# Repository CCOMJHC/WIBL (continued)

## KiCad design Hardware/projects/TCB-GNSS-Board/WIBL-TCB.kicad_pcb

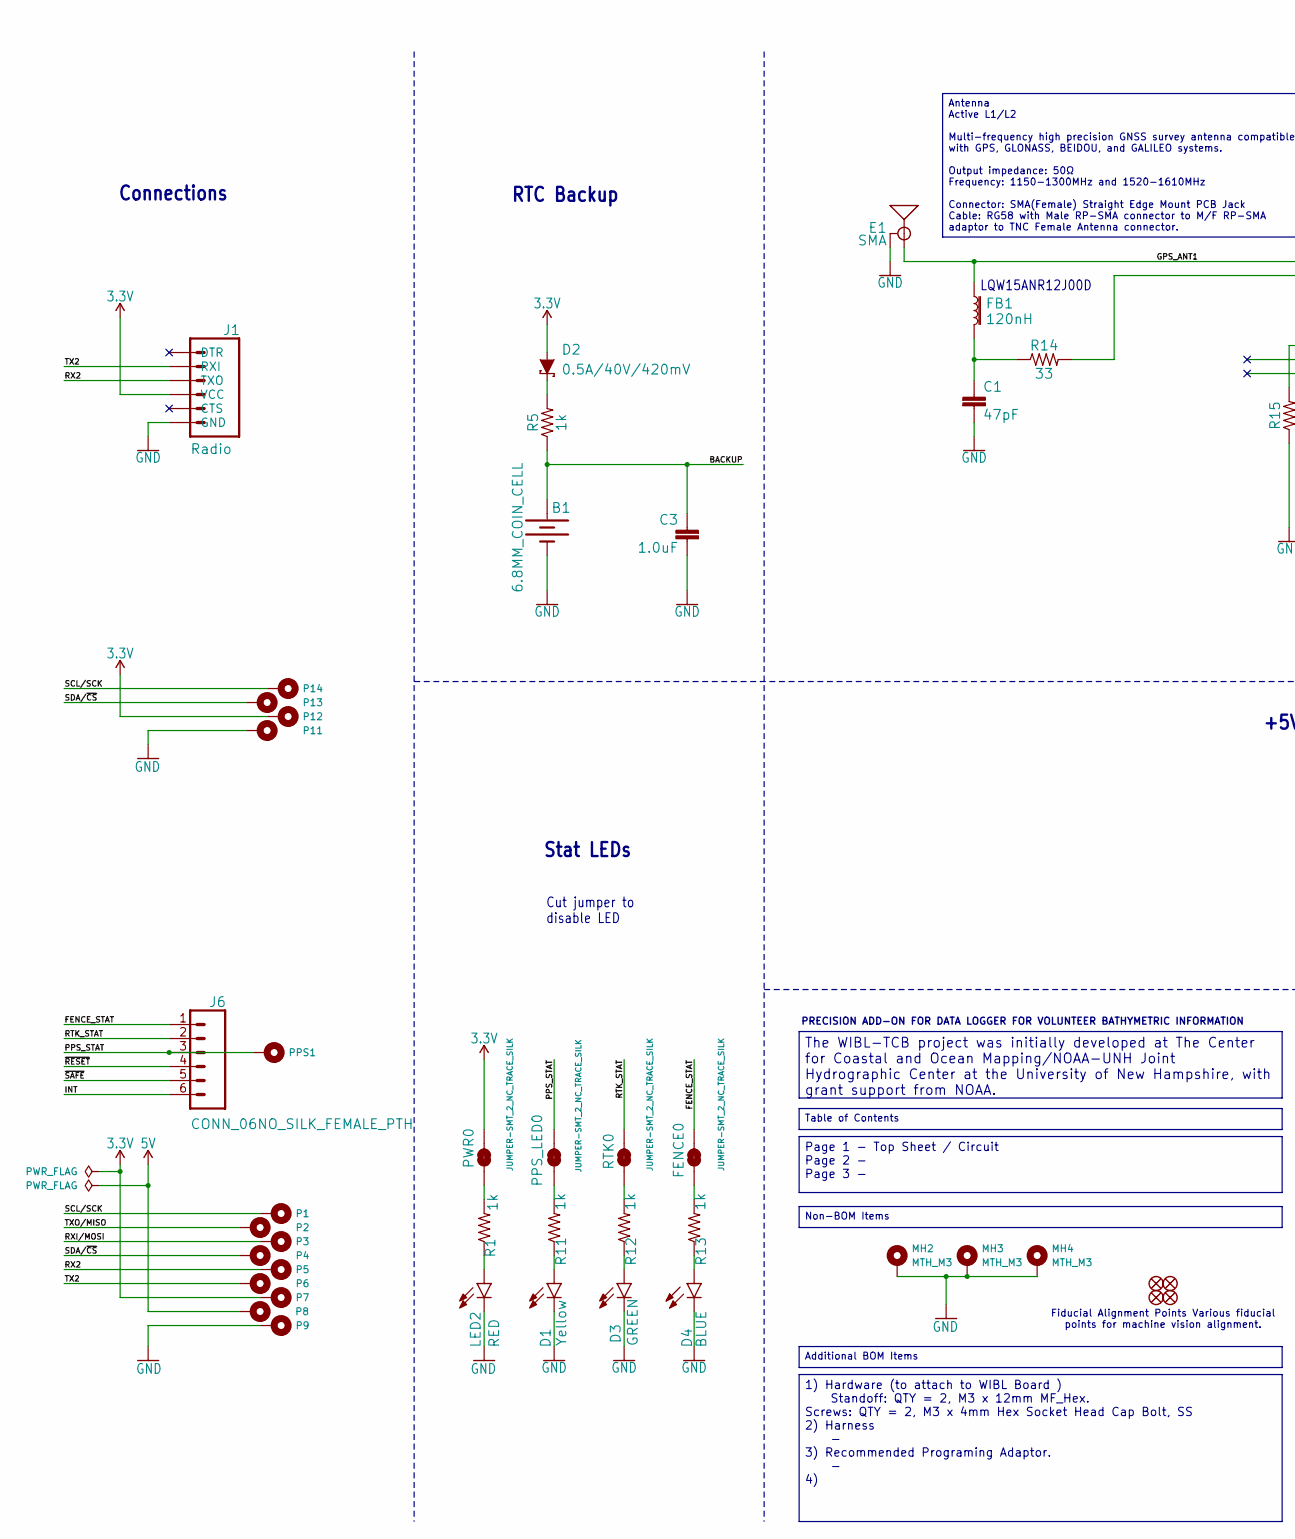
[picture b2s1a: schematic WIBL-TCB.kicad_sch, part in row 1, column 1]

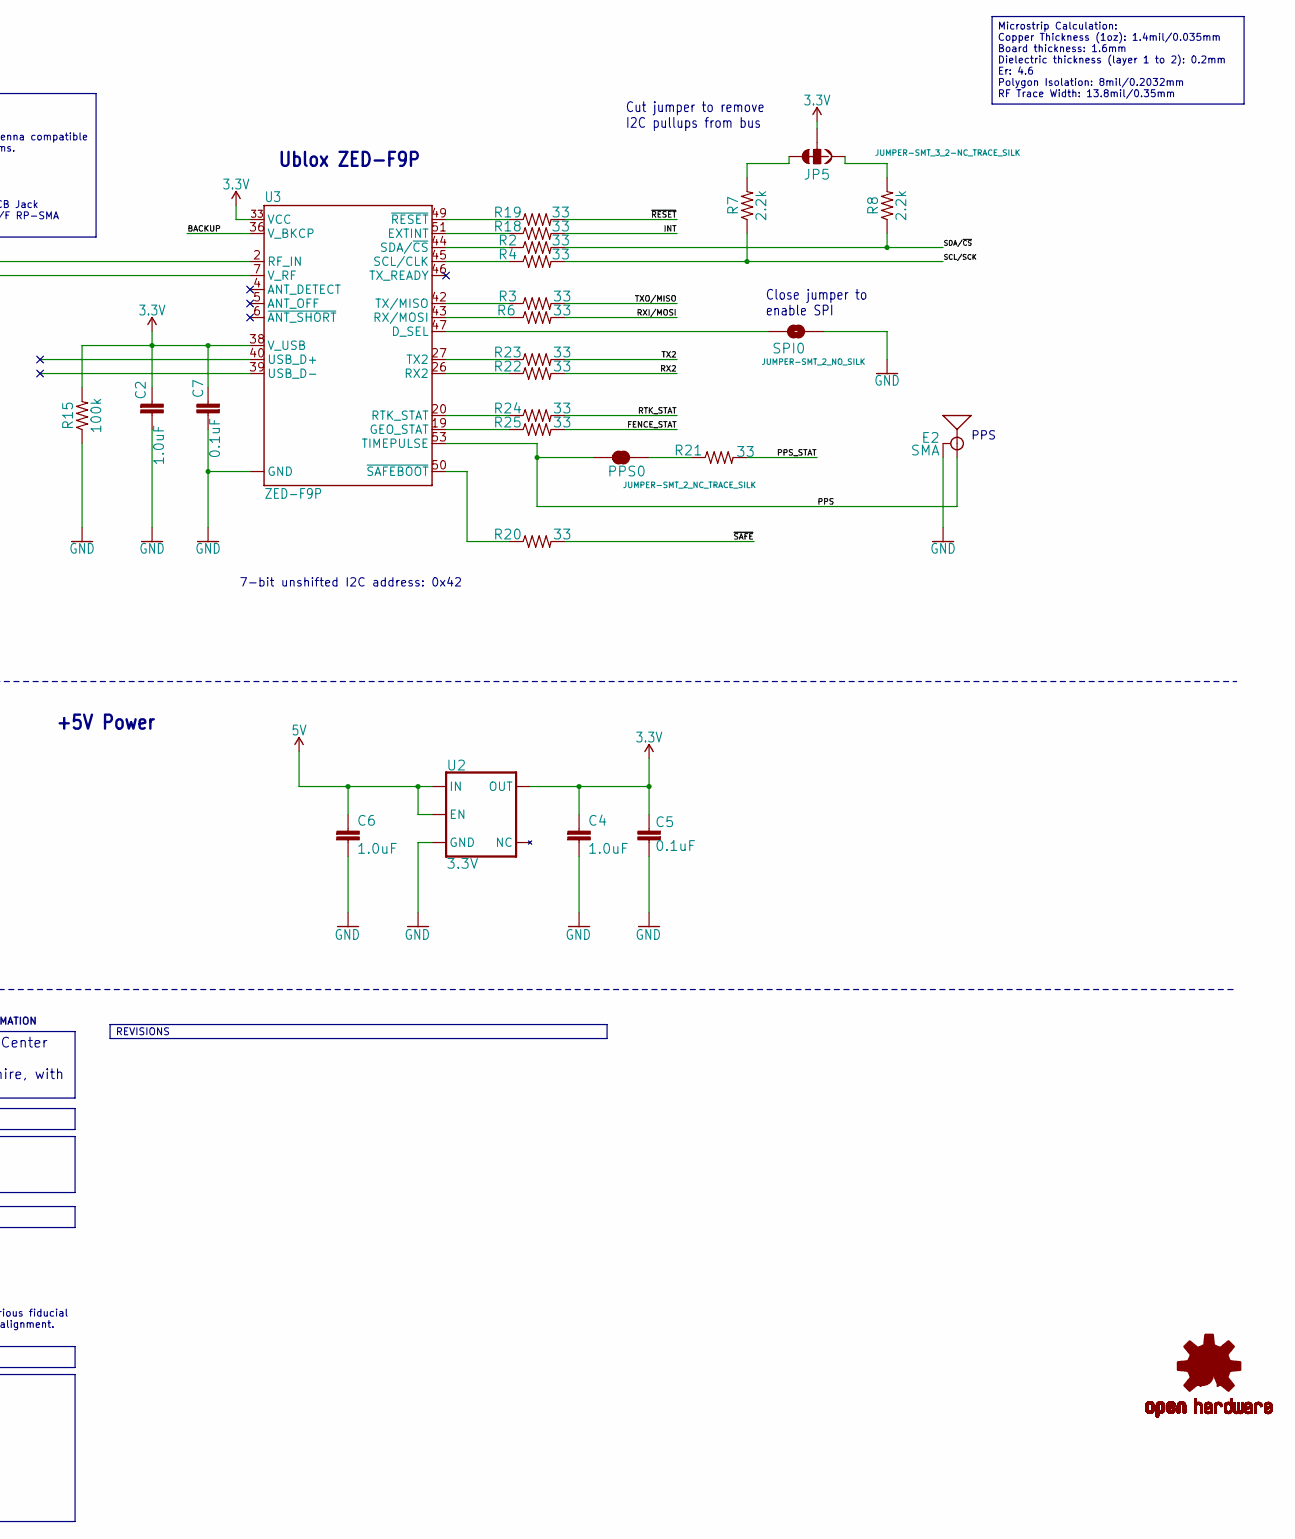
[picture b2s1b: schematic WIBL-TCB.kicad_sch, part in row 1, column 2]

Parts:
B1: 6.8MM_COIN_CELL; ML414H_IV01E_TBC; MPNum ML414H IV01E
C1: 47pF; 0402; MPNum CC0402KRNPO9BN470
C2, C3, C4, C6: 1.0uF; 0603; MPNum CL10B105KP8NNNC
C5, C7: 0.1uF; 0603; MPNum CC0603KRX7R9BB104
D1: Yellow; LED-0603; MPNum XL-1608UYC-06
D2: 0.5A/40V/420mV; SOD-323; MPNum 1N5819WS
D3: GREEN; LED-0603; MPNum LTST-C190GKT
D4: BLUE; LED-0603; MPNum LTST-C193TBKT-5A
E1, E2: SMA; SMA-EDGE; MPNum CON-SMA-EDGE-S
FB1: 120nH; 0402_MURATA; MPNum LQW15ANR12J00D
FENCE0: JUMPER-SMT_2_NC_TRACE_SILK; SolderJumper-2_P1.3mm_Bridged2Bar_RoundedPad1.0x1.5mm_TCB
J1: Radio; 1X06_NO_SILK; MPNum 61300611121
J6: CONN_06NO_SILK_FEMALE_PTH; 1X06_NO_SILK; MPNum 61300611121
JP5: JUMPER-SMT_3_2-NC_TRACE_SILK; SolderJumper-3_P1.3mm_Bridged2Bar123_RoundedPad1.0x1.5mm_TCB
JP21, JP61, JP71, JP81: FIDUCIALUFIDUCIAL; MICRO-FIDUCIAL
LED2: RED; LED-0603; MPNum XL-1608VRC-06
LOGO3: OSHW-LOGO-MINI
MH2, MH3, MH4: MTH_M3; MountingHole_3.2mm_M3
P1, P2, P3, P4, P5, P6, P7, P8, P9, P11, P12, P13, P14: PTH_D1.9mm_Drill1.1mm
PPS0: JUMPER-SMT_2_NC_TRACE_SILK; SolderJumper-2_P1.3mm_Bridged2Bar_RoundedPad1.0x1.5mm_TCB
PPS1: PTH_D1.9mm_Drill1.1mm
PPS_LED0: JUMPER-SMT_2_NC_TRACE_SILK; SolderJumper-2_P1.3mm_Bridged2Bar_RoundedPad1.0x1.5mm_TCB
PWR0: JUMPER-SMT_2_NC_TRACE_SILK; SolderJumper-2_P1.3mm_Bridged2Bar_RoundedPad1.0x1.5mm_TCB
R1, R5, R11, R12, R13: 1k; 0603; MPNum RC0603FR-071KL
R2, R3, R4, R6, R14, R18, R19, R20, R21, R22, R23, R24, R25: 33; 0603; MPNum RC0603FR-0733RL
R7, R8: 2.2k; 0603; MPNum RC0603FR-072K2L
R15: 100k; 0603; MPNum RC0603FR-07100KL
RTK0: JUMPER-SMT_2_NC_TRACE_SILK; SolderJumper-2_P1.3mm_Bridged2Bar_RoundedPad1.0x1.5mm_TCB
SPI0: JUMPER-SMT_2_NO_SILK; SolderJumper-2_P1.3mm_Open_RoundedPad1.0x1.5mm
U2: 3.3V; SOT23-5; MPNum AP2112K-3.3TRG1
U3: ZED-F9P; MPNum ZED-F9P-05B

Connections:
3.3V: C2.1, C4.1, C5.2, C7.2, D2.A, J1.4 (VCC), JP5.2, P7.1 (1_1), P12.1 (1_1), PWR0.2, R15.2, U2.5 (OUT), U3.33 (VCC), U3.34 (VCC), U3.38 (V_USB)
5V: C6.1, P8.1 (1_1), U2.1 (IN), U2.3 (EN)
/BACKUP: B1.+, C3.1, R5.1, U3.36 (V_BKCP)
/FENCE_STAT: FENCE0.2, J6.1, R25.2
/GPS_ANT1: E1.SIG (SIGNAL), FB1.P1 (1), U3.2 (RF_IN)
/INT: J6.6, R18.2
/PPS: E2.SIG (SIGNAL), PPS0.2, U3.53 (TIMEPULSE)
/PPS_STAT: J6.3, PPS1.1 (1_1), PPS_LED0.2, R21.2
/RTK_STAT: J6.2, R24.2, RTK0.2
/RX2: J1.3 (TXO), P5.1 (1_1), R22.2
/RXI/MOSI: P3.1 (1_1), R6.2
/SCL/SCK: P1.1 (1_1), P14.1 (1_1), R4.2, R7.1
/SDA/~CS: P4.1 (1_1), P13.1 (1_1), R2.2, R8.1
/TX2: J1.2 (RXI), P6.1 (1_1), R23.2
/TXO/MISO: P2.1 (1_1), R3.2
/~RESET: J6.4, R19.2
/~SAFE: J6.5, R20.2
GND: B1.-, C1.2, C2.2, C3.2, C4.2, C5.1, C6.2, C7.1, D1.C, D3.C, D4.C, E1.GND@0 (GND), E1.GND@1 (GND), E1.GND@2 (GND), E1.GND@3 (GND), E2.GND@0 (GND), E2.GND@1 (GND), E2.GND@2 (GND), E2.GND@3 (GND), J1.6 (GND), LED2.C, MH2.1 (1_1), MH3.1 (1_1), MH4.1 (1_1), P9.1 (1_1), P11.1 (1_1), R15.1, SPI0.1, U2.2 (GND), U3.1 (GND), U3.3 (GND), U3.12 (GND), U3.14 (GND), U3.32 (GND), U3.37 (GND), U3.41 (GND), U3.48 (GND), U3.55 (GND), U3.56 (GND), U3.57 (GND), U3.58 (GND), U3.59 (GND), U3.60 (GND), U3.61 (GND), U3.62 (GND), U3.63 (GND), U3.64 (GND), U3.65 (GND), U3.66 (GND), U3.67 (GND), U3.68 (GND), U3.69 (GND), U3.70 (GND), U3.71 (GND), U3.72 (GND), U3.73 (GND), U3.74 (GND), U3.75 (GND), U3.76 (GND), U3.77 (GND), U3.78 (GND), U3.79 (GND), U3.80 (GND), U3.81 (GND), U3.82 (GND), U3.83 (GND), U3.84 (GND), U3.85 (GND), U3.86 (GND), U3.87 (GND), U3.88 (GND), U3.89 (GND), U3.90 (GND), U3.91 (GND), U3.92 (GND), U3.93 (GND), U3.94 (GND), U3.95 (GND), U3.96 (GND), U3.97 (GND), U3.98 (GND), U3.99 (GND), U3.100 (GND), U3.101 (GND), U3.102 (GND)
unnamed: D1.A, R11.1
unnamed: D2.C, R5.2
unnamed: D3.A, R12.1
unnamed: D4.A, R13.1
unnamed: C1.1, FB1.P2 (2), R14.1
unnamed: FENCE0.1, R13.2
unnamed: JP5.1, R8.2
unnamed: JP5.3, R7.2
unnamed: LED2.A, R1.1
unnamed: PPS0.1, R21.1
unnamed: PPS_LED0.1, R11.2
unnamed: PWR0.1, R1.2
unnamed: R12.2, RTK0.1
unnamed: SPI0.2, U3.47 (D_SEL)
unnamed: R18.1, U3.51 (EXTINT)
unnamed: R25.1, U3.19 (GEO_STAT)
unnamed: R24.1, U3.20 (RTK_STAT)
unnamed: R22.1, U3.26 (RX2)
unnamed: R6.1, U3.43 (RX/MOSI)
unnamed: R4.1, U3.45 (SCL/CLK)
unnamed: R2.1, U3.44 (SDA/~CS)
unnamed: R23.1, U3.27 (TX2)
unnamed: R3.1, U3.42 (TX/MISO)
unnamed: R14.2, U3.7 (V_RF)
unnamed: R19.1, U3.49 (~RESET)
unnamed: R20.1, U3.50 (~SAFEBOOT)

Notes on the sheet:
7-bit unshifted I2C address: 0x42
RTC Backup
Cut jumper to disable LED
PPS
Connections
Stat LEDs
Ublox ZED-F9P
LQW15ANR12J00D
Fiducial Alignment Points Various fiducial points for machine vision alignment.
+5V Power
Cut jumper to remove I2C pullups from bus
Close jumper to enable SPI
PRECISION ADD-ON FOR DATA LOGGER FOR VOLUNTEER BATHYMETRIC INFORMATION
REVISIONS
Antenna Active L1/L2 Multi-frequency high precision GNSS survey antenna compatible with GPS, GLONASS, BEIDOU, and GALILEO systems. Output impedance: 50Ω Frequency: 1150-1300MHz and 1520-1610MHz Connector: SMA(Female) Straight Edge Mount PCB Jack Cable: RG58 with Male RP-SMA connector to M/F RP-SMA 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
Non-BOM Items
The WIBL-TCB project was initially developed at The Center for Coastal and Ocean Mapping/NOAA-UNH Joint Hydrographic Center at the University of New Hampshire, with grant support from NOAA.
Microstrip Calculation: Copper Thickness (1oz): 1.4mil/0.035mm Board thickness: 1.6mm Dielectric thickness (layer 1 to 2): 0.2mm Er: 4.6 Polygon Isolation: 8mil/0.2032mm RF Trace Width: 13.8mil/0.35mm
Additional BOM Items
1) Hardware (to attach to WIBL Board ) Standoff: QTY = 2, M3 x 12mm MF_Hex. Screws: QTY = 2, M3 x 4mm Hex Socket Head Cap Bolt, SS 2) Harness - 3) Recommended Programing Adaptor. - 4)
Table of Contents
Page 1 - Top Sheet / Circuit Page 2 - Page 3 -

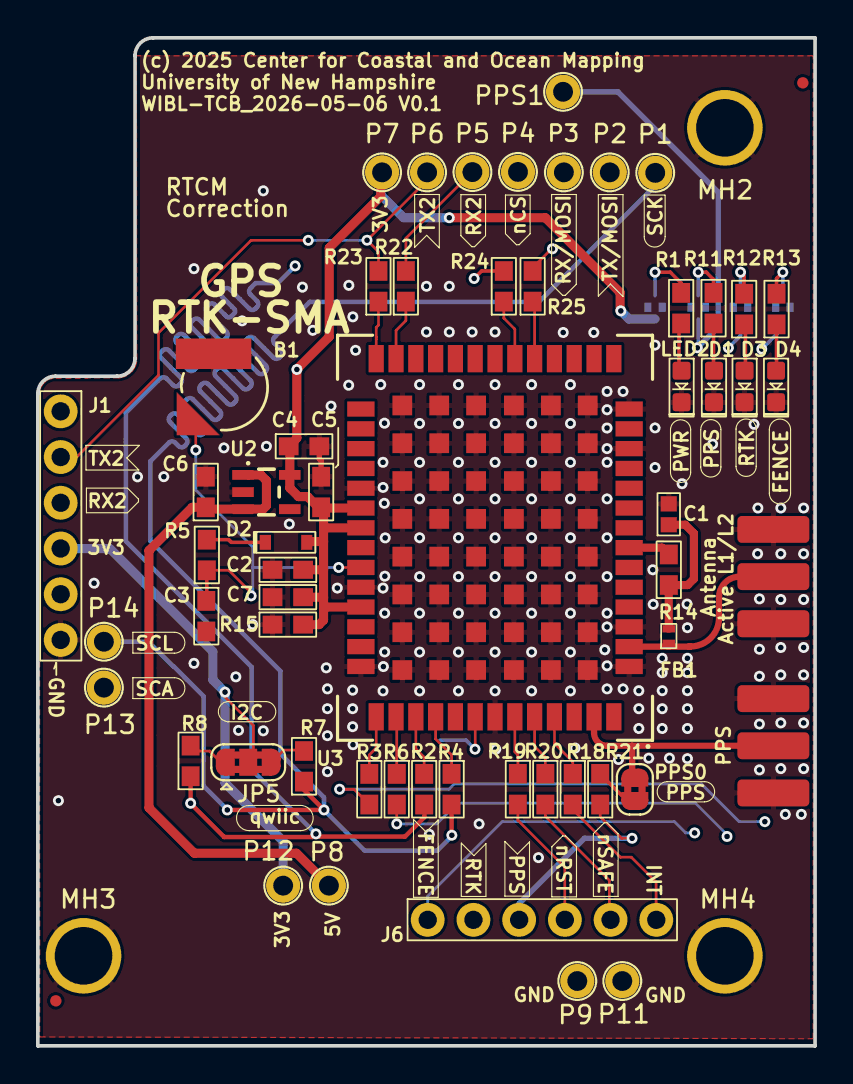
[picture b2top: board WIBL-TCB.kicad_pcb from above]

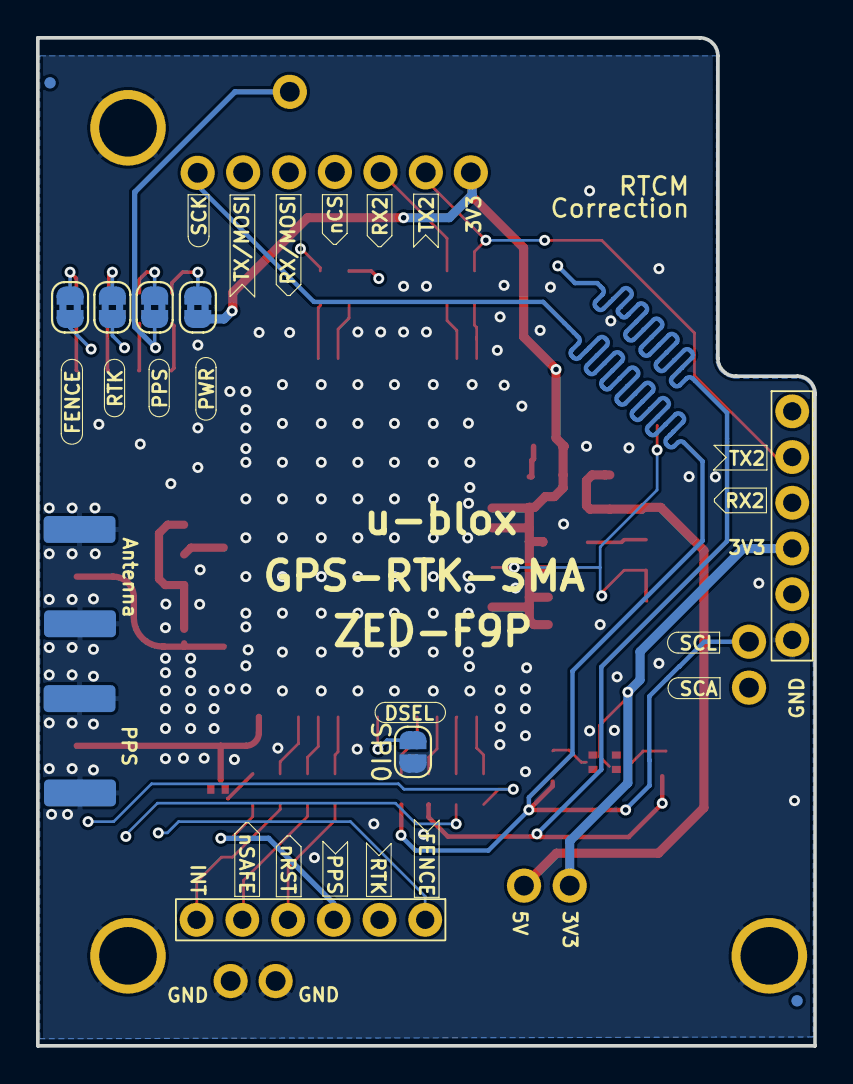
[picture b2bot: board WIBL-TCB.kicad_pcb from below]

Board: 4 copper layers, 43.2 x 56.0 mm, 69 parts (7 on the bottom side), 44 nets.

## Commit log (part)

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2025-03-19 Fixed Localstack start up scripting
2025-03-25 New ProcessWibl
    This new version no longer exits out of the loop when a file fails to convert to GeoJSON due to a lack of information. Files unable to be transformed are documented in a CSV for record-keeping.
2025-03-26 #65 Update metadata handling on GeoJSON conversion to assume OpenVBI-compatible B-12 metadata
2025-03-27 Convert script for tsv and dat
2025-04-04 Refactor Open Layers JS into separate file
2025-04-21 Documented code.
2025-04-25 #65 Add note to README about default CRS in GeoJSON metadata templates
2025-05-07 wibl-python: Update readme: move not on metadata format to the more relevant Edit WIBL file section
2025-05-22 wibl-python: Converted processing PowerShell script to LF endings, rather than CRLF, for consistency.
2025-05-22 fw: bump version to 1.5.4
2025-05-23 fw: updated release notes for 1.5.4 release.
2025-05-23 fw: Added mDNS responder to WiFi
    This addition ensures that the WiFi system starts an mDNS responder when either the AP starts or station connects, so that the logger is resolvable as "logger.local" using any modern OS and browser.
2025-05-24 fw: release notes for 1.5.5
2025-05-27 Added validation, submission, and conversion start lambdas
2025-05-28 Bug fixes
2025-05-28 Fixed pathing
2025-05-29 lambda packaging: move to src-layout packag structure to ensure package autodiscovery is safe and reliable (more info: https://setuptools.pypa.io/en/latest/userguide/package_discovery.html#src-layout)
2025-06-01 OpenLayers Integration
2025-06-01 Restored Static Folder
2025-06-01 Created a tap that contains an empty Mapbox map.
2025-06-01 Establishing frontend and manager connection
2025-06-02 Restore accidentally deleted files
2025-06-10 WIP Geojson download
2025-06-10 Filter debugging / Linked detail table clearing
2025-06-17 Starting dashboard
2025-06-18 Get all endpoint
2025-06-23 Fixed static collection
2025-06-26 Continued Overhaul
2025-06-27 Started wibl_data transition
2025-07-02 Continued Development on wibl and geojson data transition
2025-07-07 Download and Save FastAPI implementation for WIBL/GeoJSON
2025-07-10 Changed WIBL metadata to include average lat/lon and total depth in metres.
2025-07-14 Dashboard update interval selection and polling.
2025-07-16 Separate frontend & manager into separate db containers / Migrate postgis db to include bounding boxs
2025-07-21 Refactoring out dash in place of plotly JS
2025-07-23 Static Dashboard
2025-07-25 Bounding box display on dashboard map
2025-07-28 Comments / Removed deltas / implemented observations used gauge
2025-07-29 wibl-python: Debug local-only commands after conversion to use click library
2025-07-30 wibl-python: Add localstack docker config for automated testing of uploadwibl without cloud
2025-07-30 wibl-python: Update documentation to reflect click-based CLI; Update wibl integration test to add validate command; Update test suite metadata to conform to B-12 3.1; Update config parsing to add def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
2025-07-31 wibl-python: Document strict mode processing of WIBL files
2025-07-31 Updating Doc Strings / Adding Comments
2025-08-29 fw: outline for a batch download using tar+gz library (responding to GET on a particular endpoint).
2025-09-02 fw: fixes for streaming an archived tar/gz file of all logs.
2025-09-03 fw: updates to website for archive download, bug-fixes to support. Moves command processor to 1.4.1.
2025-09-03 Adjusting GeoJSONStatus bitwise applications / GeoJSONStatus unit tests
2025-09-18 Unit test changes
2025-10-14 fw: Small edit to clean up 1.6.0 PR (82)
2025-10-15 upload-server: Add initial (not quite working) localstack configuration to allow local testing of S3 uploads; Document how to test uploads using curl
2025-10-15 upload-server: Add reference to script to build add-logger command
2025-10-15 upload-server: Add initial README
2025-10-15 upload-server: Add support for overriding AWS endpoint to facilitate local testing; Make SNS topic optional, if not defined in config, skip notification on upload
2025-10-15 upload-server: Begin refactor of configuration to make cloud deployment simpler
2025-10-15 upload-server: Refactor security group to use rules to enable both SSH and HTTPS access
2025-10-15 upload-server: Add Elastic IP so that upload server can be accessed via a persistent IP address
2025-10-15 upload-server: Add AWS access and secret to wibl-upload compose configuration used for local testing; Add example of reading bucket data via aws cli
2025-10-15 upload-server: Start sketching out terraform config
2025-10-15 upload-server: Add add-logger script to deployment
2025-10-15 upload-server: Start refactoring cert generation to use terraform TLS provider
2025-10-15 upload-server: Add policies and role for access S3 and SNS from EC2 instance
2025-10-15 upload-server: Document Terraform deployment and configuring and testing the instance
2025-10-15 upload-server: Debug userdata script to enable systemctl service for upload-server that survives reboot
2025-10-15 upload-server: Un-comment logging of CHECKIN status now that logging has been refactored
2025-10-15 upload-server: Fix typos; Add trusted node prefix to example logger identifiers
2025-10-16 upload-server: fix typos; include terraform.lock.hcl; add .terraform directory to gitignore
2025-10-20 upload-server: CloudWatch agent: Enable removal of logs that have been uploaded to CloudWatch
2025-10-27 wibl-python: cloud: AWS: Update conversion start lambda permissions as per https://docs.aws.amazon.com/lambda/latest/dg/urls-auth.html#urls-auth-none
2025-10-30 FW: Updates for supply voltage monitoring with hardware v 2.5.1, including the value being reported in status JSON, and on the website.
2025-10-30 Creating new terraform module parallel to configure-manager-ecs.sh
2025-10-31 Upload: fixed comments to reflect full implementation.
2025-11-01 Upload: added configuration parameter for CA certificate so that we can retrieve it from add-logger and report as part of the configuration package.
2025-11-04 FW: Updates to supply monitor to clean up a little.
2025-11-05 HWSim: Restructured to make N2K and N1K follow the same simulator message sequence, which limits traffic on N2K bus, but at least allows it to vary!
2025-11-07 Updated top-level README to bring things up to date.
2025-11-24 Addition of v2.5.1 hardware design files
    This archives the Eagle CAD files for 2.4.1 and adds the KiCAD files for v2.5.1, and supporting information.
2025-11-24 Renaming STEP files for enclosures for consistency.
2025-11-24 Clean-up of KiCAD project files.
2025-12-04 HW: Updates for 2.5.1 hardware release using KiCAD files.
2025-12-04 Small modification for brackets in hardware simulator (functionally identical, but safer).
2025-12-08 Updates to mechanical drawings and STLs for hardware 2.5.1 enclosures.
    Added STL files for 2.5.1 enclosures, bringing the archive up to date; added mechanical drawings for the new enclosure.
2025-12-09 upload-server: fix typo: Document Docker multi-platform builds on Linux AMD64 hosts
2025-12-11 upload-server: Add link to IAM console
2025-12-24 LogConvert: Add script to build statically linked binary in macOS
2025-12-29 Initial bug fixes
2026-01-07 Frontend RDS instance / Expanded container definitions / Cloudwatch groups / ECS one off tasks
2026-01-14 Implementing Django s3 static storage / Static file adjustments / Frontend/Manager setup task changes
2026-01-14 data-management: Update Docker image Dockerfile and documentation for 1.2.0 release
2026-01-20 Stubbing out configuration interface, library, and GNSS integration into main routine.
2026-01-23 UploadServer: Add note on configuration backend in main.tf as well as terraform.tfvars
2026-01-23 Cloudfront additions, vpc permission changes, static bucket access changes
2026-01-28 Changing Bulma to correct file extension / addressing cors issues with static files
2026-02-25 wibl-python: Update rasterio dependency to allow installation under Python 3.14
2026-03-10 UploadServer: Add note to use the DNS name for UploadServer instead of IP address when configuring loggers to do auto-uploads
2026-03-19 Fixing state implementation
2026-03-23 Update validateWibl.ps1 to have clearer failure messages
    Hi, I am so bad at github and I have no idea if this is the right way to do this. Please let me know if this works.
    I am trying to make the validation more obvious so that we don't have to search black and white text for "successfully validated ..." or "failed to vaildate..."
2026-03-26 Fix issue with mismatched commandProc versions.
2026-03-28 refinement of tweeks to ensure enough mem is avialable for dropbox upload.
2026-03-31 Fix map to include style and glyph information
2026-04-02 Add ability to convert both .dat and .tsv to .WIBL
2026-04-07 Adding SSM auth string management / Submission lambda bug fixes / Manager Statistics endpoint bug fixes
2026-05-11 Move Terraform folder into AWS folder / Add build instruction / add descriptions to variables in the main variables.tf file / remove unnecessary definition files.
2026-05-12 Allow JSON to be moved directly into the WiFi message buffer
    I'm running into situations where a large JSON document is being
    successfully generated, but then allocation fails when trying to copy
    it into ESP32WiFiAdapter::m_messages.
    Move semantics to the rescue!
2026-05-12 Store ESP32WiFiAdapter::m_messages by value instead of pointer
    Keeping the document itself on the heap only introduced complexity
    which we didn't really need.
    Also store the default buffer size in a named constant.
2026-05-12 Show question marks for missing file detail fields
    Previously any missing field would cause the whole row to be dropped.
    Given that MD5 hashes aren't guaranteed to be present, that felt like
    overkill.
2026-05-12 Avoid holding a large JSON document while initiating SSL connections
    We ran into issues with allocation failures when attempting to set up
    SSL connections. After a lot of searching and trial-and-error, we
    realized that as the number of log files on the SD card grew, the size
    of the JSON document returned by GenerateFilelist() grew to consume a
    significant chunk of heap memory. This document was resident while the
    upload loop ran, which is the exact time we needed the memory most.
2026-05-12 Allow CountLogFiles to optionally determine total size
    My goal is to pull the file list out of the status JSON document, which
    will require calculating the total file count and size separately from
    the full file list.
2026-05-12 Documentation changes / removing commented code / adding extra nat gateway and routing table for public/private subnet 2
2026-05-15 Adding s3 state storage for the wibl-python terraform configuration
2026-05-18 Adding secret generation script, changing readme to include the script.
2026-05-18 Fixing statistics endpoint bug / Adding plotly as static instead of cdn delivery / removing commented out code
2026-05-19 Add optional WPA3/PMF configuration parameters for Station mode (#111)
    - Adds CONFIG_REQUIRE_PMF_S to allow users with modern hotspots (like Pixel 9 Pro) to enforce Protected Management Frames.
    - Defaults PMF to capable but not required to preserve compatibility with legacy WPA2 networks.
    - Sets sae_pwe_h2e to WPA3_SAE_PWE_BOTH where available to enable WPA3 SAE flow.
2026-05-19 feat(wifi): implement async AP fallback and hotspot recovery scanning
    Replaces the hard ESP.restart() failure loop when Station connection exhausts its retries. Instead:
    - State machine drops to AP-Fallback mode headlessly via apSetup()
    - Triggers non-blocking background async scans WiFi.scanNetworks(true)
    - Polls for configured hotspot presence over the air
    - Transitions seamlessly back to Station mode if detected
    - Configured via new parameter CONFIG_STATION_SCAN_INTERVAL_S exposed to Web UI (default: 30000 ms / 30s)
2026-05-19 fix(wifi): robust WPA3 baseband reset and connection retry handling
2026-05-20 Updating README to account for manual variable replacement in the s3 state storage module.
2026-05-27 Fixing the bounding box bug.
2026-05-27 Updated README for upload server, and pinned localstack (for local test) to v.4.8.1 so that we can run without having to use a license.
2026-05-28 Updating documentation / Removing auth files from git (tfvars, default_auth) / Changing file names / Adding prototype files
